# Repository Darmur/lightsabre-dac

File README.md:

# lightsabre-dac
Audiophile DAC for Raspberry Pi, based on ESS Sabre ES9018K2M

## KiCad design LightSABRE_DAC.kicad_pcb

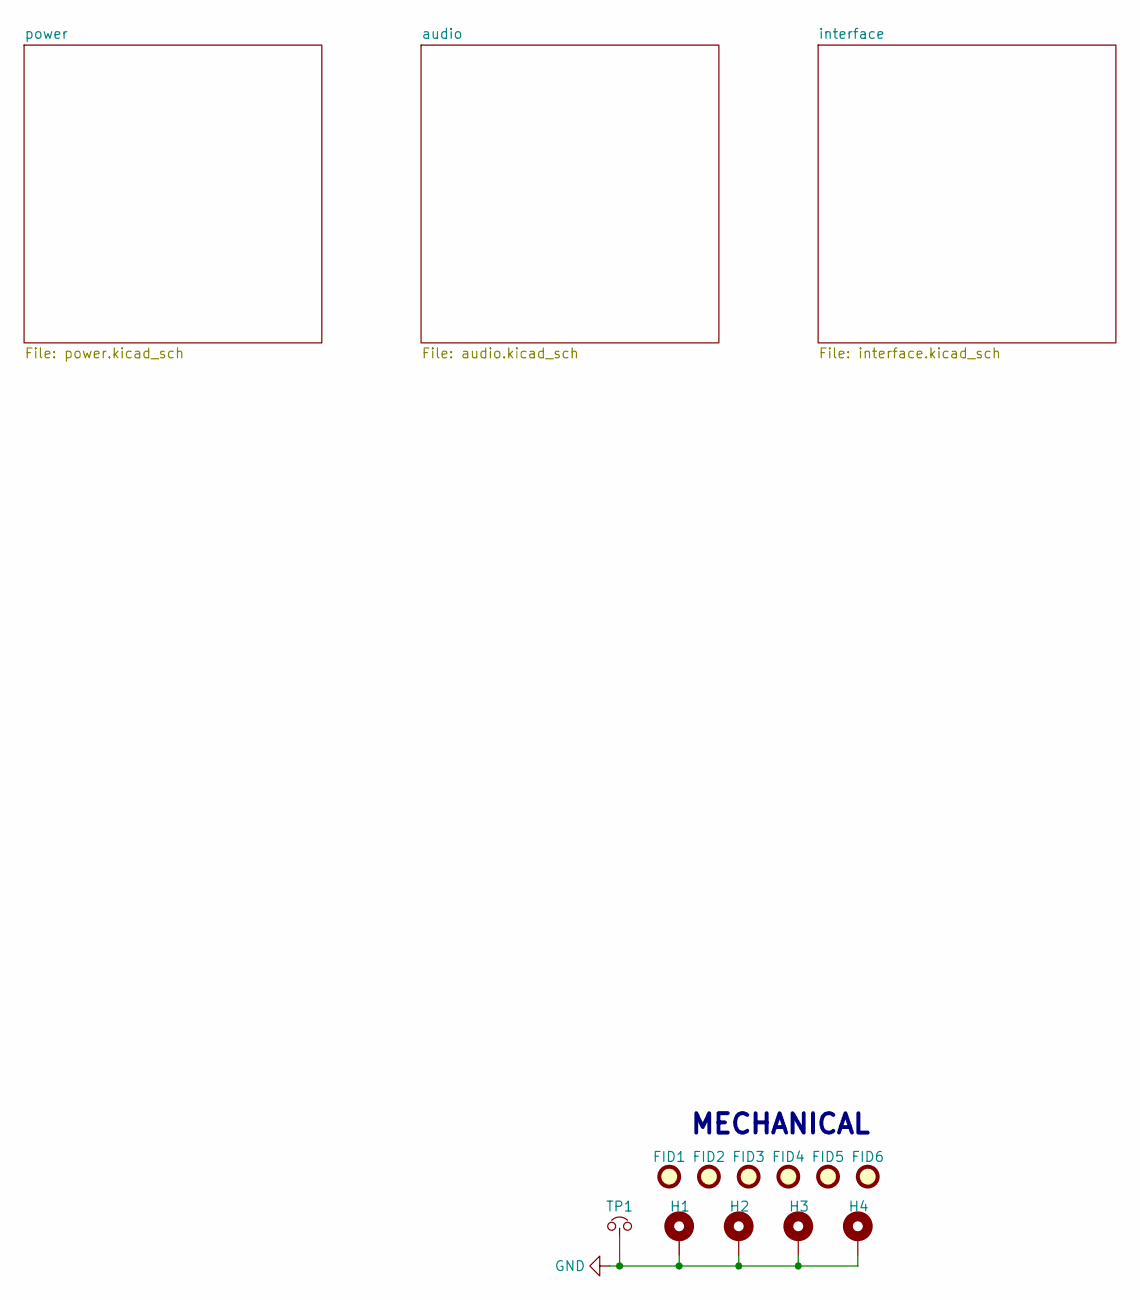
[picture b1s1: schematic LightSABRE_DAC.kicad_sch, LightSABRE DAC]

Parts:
FID1, FID2, FID3, FID4, FID5, FID6: FID_001; Fiducial_0.5mm_Mask1mm; MPN N.M.; LCSC N.M.
H1, H2, H3, H4: MOUNTING-HOLE-M2.5-SMALL; MOUNTING-HOLE-M2.5-ROUND-2.7MM-3.2MM; MPN N.M.; LCSC N.M.
TP1: GND-TP; TestPoint_Bridge_Pitch7.62mm_Drill1.3mm; MPN N.M.; LCSC N.M.

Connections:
GND: H1.1, H2.1, H3.1, H4.1, TP1.1; also elsewhere on the board

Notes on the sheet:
MECHANICAL

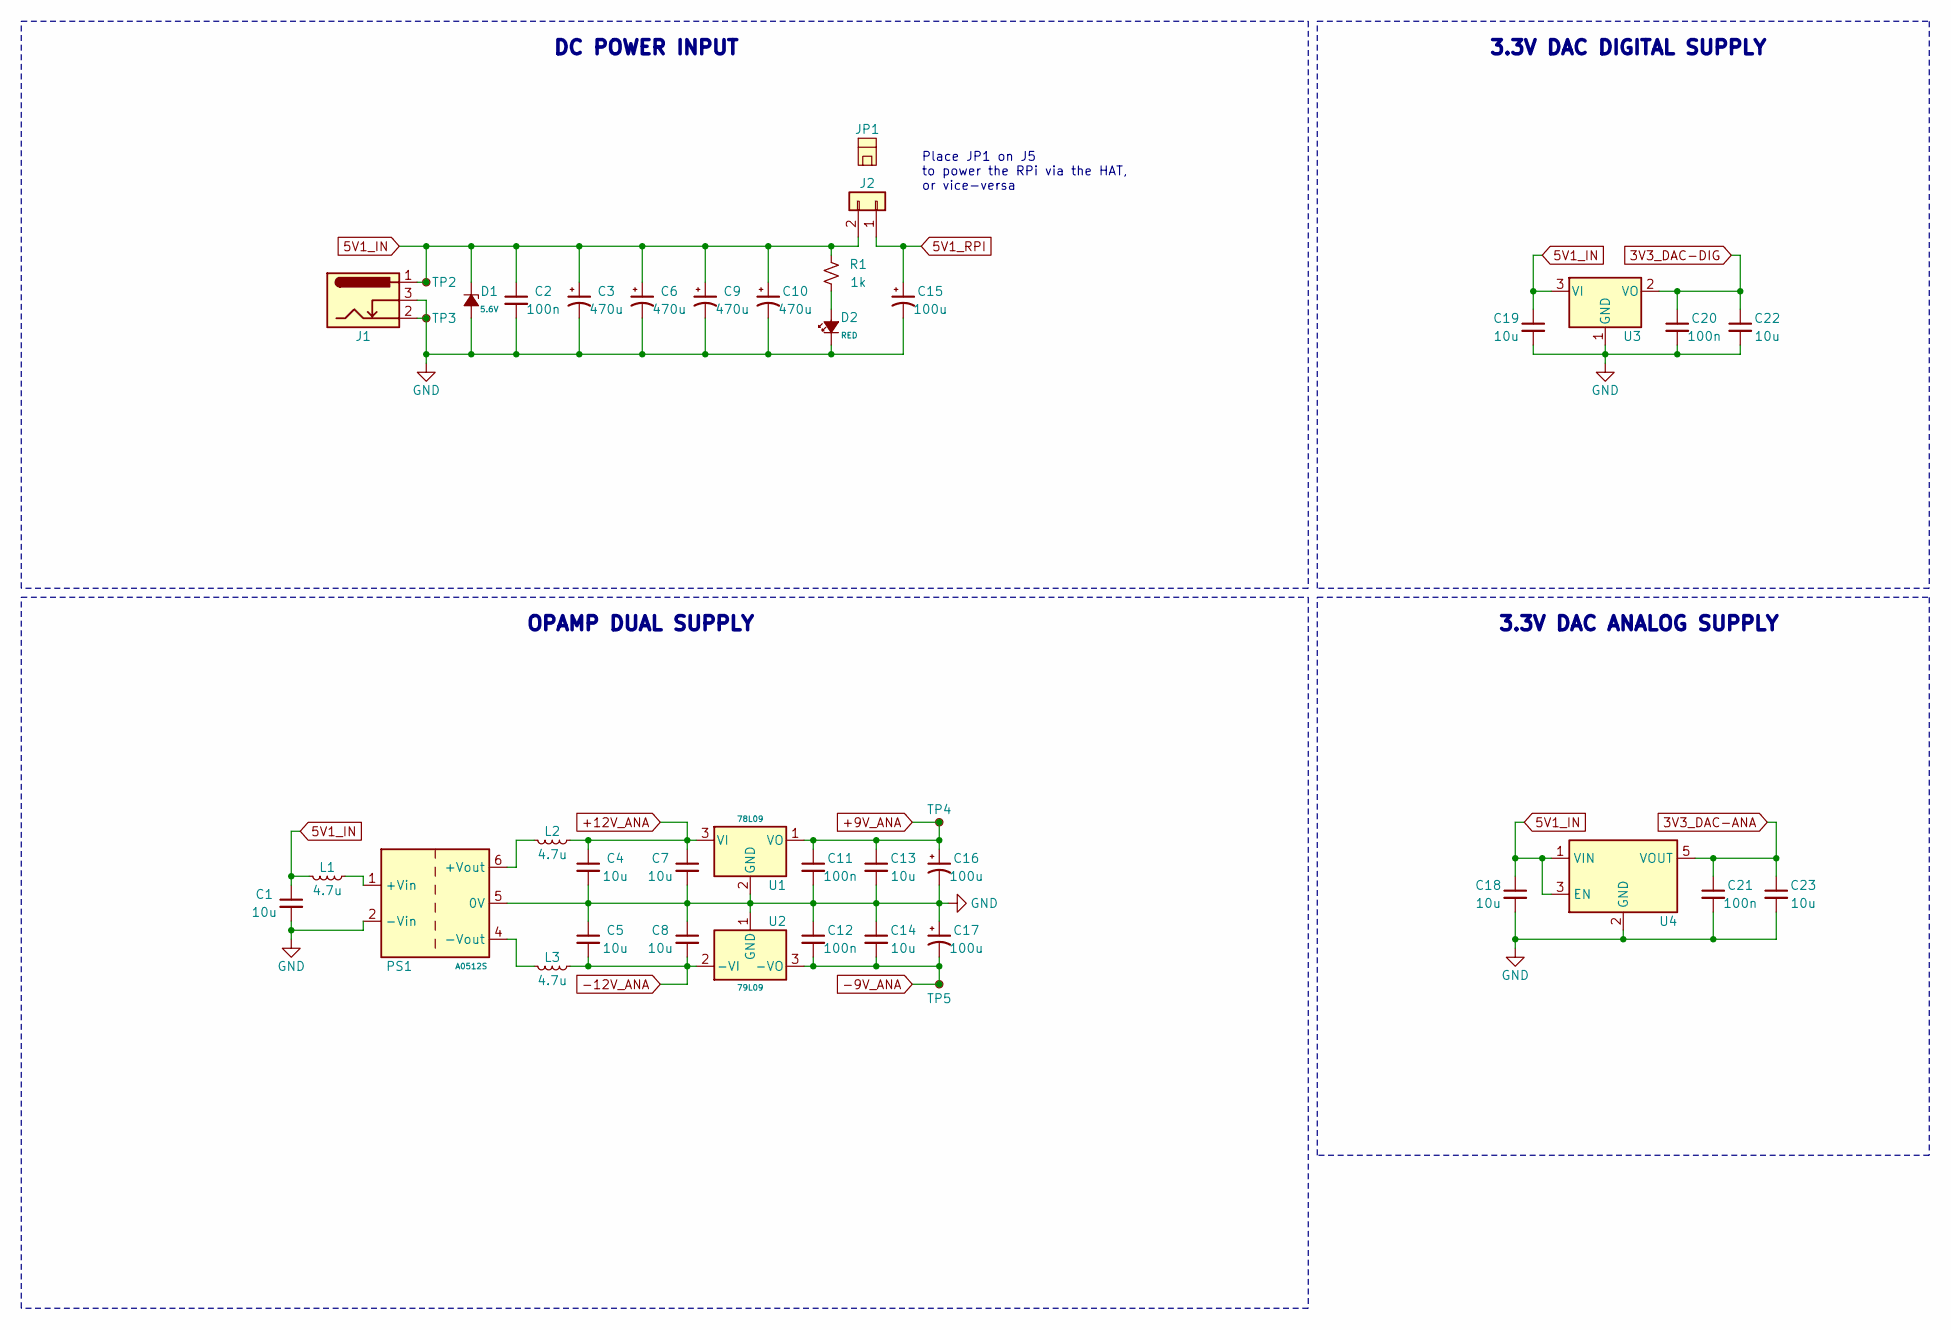
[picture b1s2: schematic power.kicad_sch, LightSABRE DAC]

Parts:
C1, C4, C5, C7, C8, C13, C14, C18, C19, C22, C23: CAP-10U-20%-16V-X5R-0603_004; C_0603_1608Metric; MPN HGC0603R5106M160NTHJ; LCSC C7472959
C2, C11, C12: CAP-100N-10%-50V-X7R-0603_002; C_0603_1608Metric; MPN CGA0603X7R104K500JT; LCSC C6119867
C3, C6, C9, C10: CAP-EL-470U-20%-10V-ALUM-6.3MM-7.7MM_002; CP_Elec_6.3x7.7; MPN RVT1A471M0607; LCSC C335982
C15, C16, C17: CAP-EL-100U-20%-16V-ALUM-5.0MM-5.4MM_002; CP_Elec_5x5.4; MPN RVT1C101M0505; LCSC C2977550
C20, C21: CAP-100N-10%-16V-X7R-0402_002; C_0402_1005Metric; MPN FCC0402B104K160AT; LCSC C5137468
D1: ZENER-5.6V-5W-SMB_003; D_SMB; Voltage 5.6V; MPN SMBJ5339B; LCSC C5122124
D2: LED-RED-0402_002; LED_0402_1005Metric; MPN XL-1005SURC; LCSC C25503345
J1: BARREL-JACK-SW_002; BarrelJack; MPN DC-005 5.5-2.0MM; LCSC C16214
J2: CONN-HDR-01X02-2.54-TH_002; PinHeader_2x01_P2.54mm_Vertical; MPN C124375; LCSC C124375
JP1: CONN-SHUNT-2P-2.54MM-BLACK-CAPPED_002; MPN HY-2540-B1NIB; LCSC C18185738
L1, L2, L3: IND-4.7U-20%-1.55A-0.196OHM-1008_002; L_1008_2520Metric; MPN WIP252012P-4R7ML; LCSC C964123
PS1: A0512S-2W-1.5KV-SIP_002; Converter_DCDC_XP_POWER-IHxxxxS_THT; MPN A0512S-2WR2; LCSC C5369424
R1: RES-1K-5%-0.063W-0402_002; R_0402_1005Metric; MPN 0402WGJ0102TCE; LCSC C25543
TP2, TP3, TP4, TP5: TP-TH-ROUND-1MM-0.5MM; TestPoint_THTPad_D1.0mm_Drill0.5mm; MPN N.M.; LCSC N.M.
U1: 78L09-SOT89_002; SOT-89-3; MPN 78L09; LCSC C22458782
U2: 79L09-SOT89_002; SOT-89-3; MPN PJ79L09SQ; LCSC C41784049
U3: LR6206B-U33; SOT-23; MPN LR6206B-U33; LCSC C5336486
U4: TPS7A2033-SOT23; SOT-23-5; MPN TPS7A2033PDBVR; LCSC C2862740

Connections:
3V3_DAC-ANA: C21.1, C23.1, U4.5 (VOUT); also elsewhere on the board
3V3_DAC-DIG: C20.1, C22.1, U3.2 (VO); also elsewhere on the board
5V1_IN: C1.1, C2.1, C3.1, C6.1, C9.1, C10.1, C18.1, C19.1, D1.1 (K), J1.1, J2.2, L1.2, R1.1, TP2.1, U3.3 (VI), U4.1 (VIN), U4.3 (EN); also elsewhere on the board
5V1_RPI: C15.1, J2.1; also elsewhere on the board
+9V_ANA: C11.1, C13.1, C16.1, TP4.1, U1.1 (VO); also elsewhere on the board
+12V_ANA: C4.1, C7.1, L2.1, U1.3 (VI)
-9V_ANA: C12.2, C14.2, C17.2, TP5.1, U2.3 (-VO); also elsewhere on the board
-12V_ANA: C5.2, C8.2, L3.1, U2.2 (-VI)
GND: C1.2, C2.2, C3.2, C4.2, C5.1, C6.2, C7.2, C8.1, C9.2, C10.2, C11.2, C12.1, C13.2, C14.1, C15.2, C16.2, C17.1, C18.2, C19.2, C20.2, C21.2, C22.2, C23.2, D1.2 (A), D2.1 (K), J1.2, J1.3, PS1.2 (-Vin), PS1.5 (0V), TP3.1, U1.2 (GND), U2.1 (GND), U3.1 (GND), U4.2 (GND); also elsewhere on the board
unnamed: D2.2 (A), R1.2
unnamed: L1.1, PS1.1 (+Vin)
unnamed: L2.2, PS1.6 (+Vout)
unnamed: L3.2, PS1.4 (-Vout)

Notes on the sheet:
DC POWER INPUT
3.3V DAC DIGITAL SUPPLY
OPAMP DUAL SUPPLY
3.3V DAC ANALOG SUPPLY
Place JP1 on J5 to power the RPi via the HAT, or vice-versa

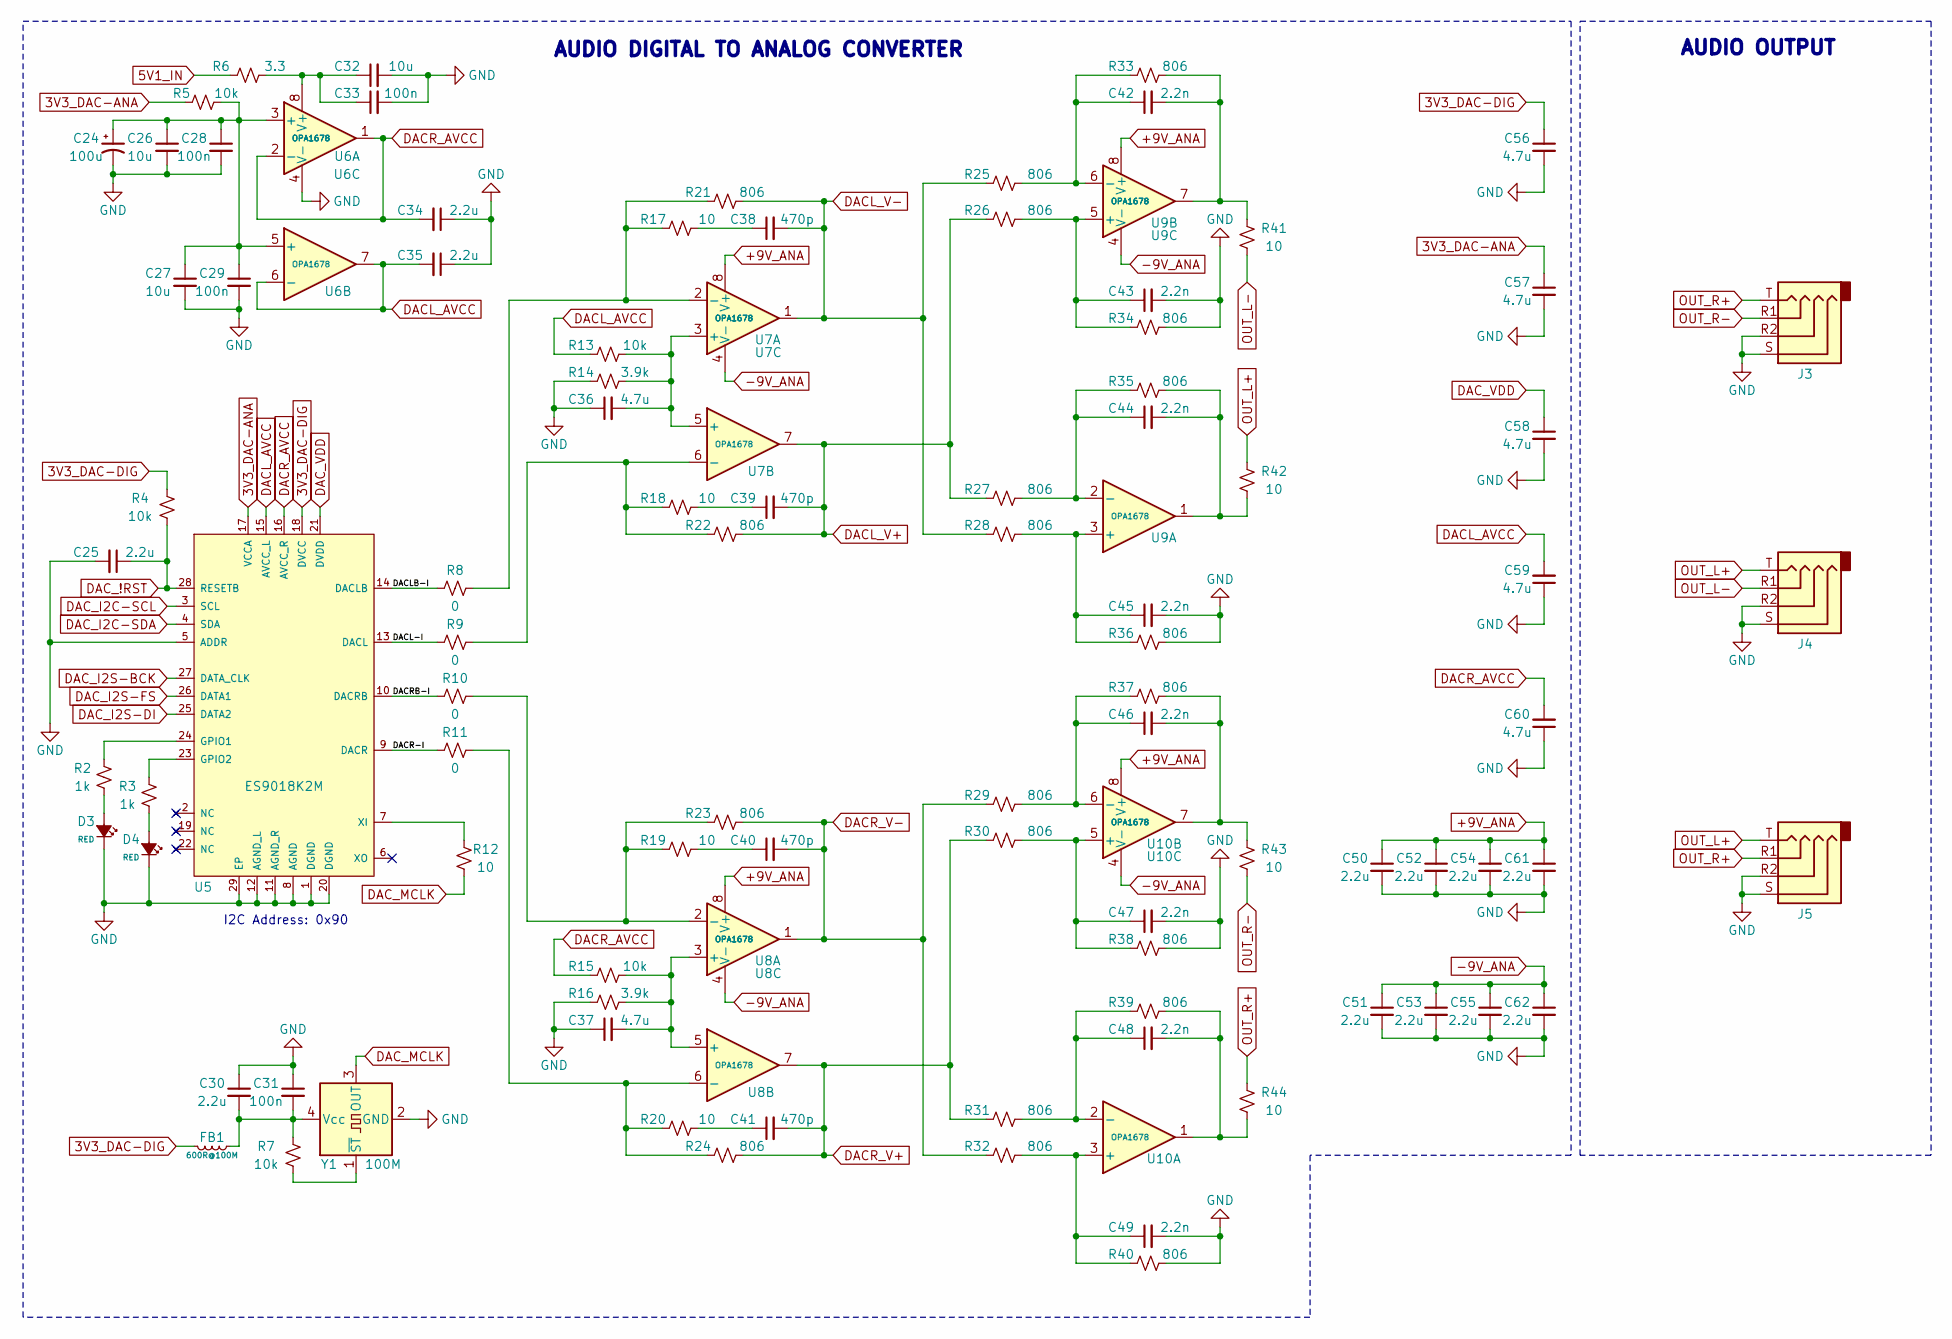
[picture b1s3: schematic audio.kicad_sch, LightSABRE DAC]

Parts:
C24: CAP-EL-100U-20%-16V-ALUM-5.0MM-5.4MM_002; CP_Elec_5x5.4; MPN RVT1C101M0505; LCSC C2977550
C25, C30, C34, C35, C50, C51, C52, C53, C54, C55, C61, C62: CAP-2.2U-20%-16V-X5R-0402_002; C_0402_1005Metric; MPN CGA0402X5R225M160GT; LCSC C6119773
C26, C27, C32: CAP-10U-20%-16V-X5R-0603_004; C_0603_1608Metric; MPN HGC0603R5106M160NTHJ; LCSC C7472959
C28, C29, C31, C33: CAP-100N-10%-16V-X7R-0402_002; C_0402_1005Metric; MPN FCC0402B104K160AT; LCSC C5137468
C36, C37, C56, C57, C58, C59, C60: CAP-4.7U-20%-10V-X5R-0402_002; C_0402_1005Metric; MPN HGC0402R5475M100NTEJ; LCSC C7472957
C38, C39, C40, C41: CAP-470P-5%-50V-C0G-0402_002; C_0402_1005Metric; MPN CGA0402C0G471J500GT; LCSC C20069335
C42, C43, C44, C45, C46, C47, C48, C49: CAP-2.2N-2%-50V-C0G-0402_001; C_0402_1005Metric; MPN GRM1555C1H222GA01D; LCSC C2987940
D3, D4: LED-RED-0402_002; LED_0402_1005Metric; MPN XL-1005SURC; LCSC C25503345
FB1: FERR-BEAD-600OHM@100MHZ-0.7A-0.34OHM-0402; L_0402_1005Metric; MPN PBY100505T-601Y-N; LCSC C142082
J3, J4, J5: PJ-320A; TRRS-PJ-320A; MPN PJ-320A; LCSC C2884926
R2, R3: RES-1K-5%-0.063W-0402_002; R_0402_1005Metric; MPN 0402WGJ0102TCE; LCSC C25543
R4, R5, R7, R13, R15: RES-10K-1%-0.063W-0402_002; R_0402_1005Metric; MPN RTT021002FTH; LCSC C102749
R6: RES-3.3-1%-0.1W-0603_002; R_0603_1608Metric; MPN FRC0603F3R30TS; LCSC C2930016
R8, R9, R10, R11: RES-0-1%-0.1W-0603_002; R_0603_1608Metric; MPN FRC0603F0000TS; LCSC C2906974
R12, R17, R18, R19, R20, R41, R42, R43, R44: RES-10-1%-0.063W-0402_002; R_0402_1005Metric; MPN FRC0402F10R0TS; LCSC C2906862
R14, R16: RES-3.9K-1%-0.063W-0402_002; R_0402_1005Metric; MPN FRC0402F3901TS; LCSC C2909346
R21, R22, R23, R24, R25, R26, R27, R28, R29, R30, R31, R32, R33, R34, R35, R36, R37, R38, R39, R40: RES-806-0.1%-0.063W-THIN-0402_001; R_0402_1005Metric; MPN RT0402BRD07806RL; LCSC C852922
U5: ES9018K2M; QFN-28-1EP_5x5mm_P0.5mm_EP3.25x3.25mm_ThermalVias_0.3mm; MPN ES9018K2M; LCSC C2688377
U6, U7, U8, U9, U10: OPA1678-VSSOP; MSOP-8_3x3mm_P0.65mm; MPN OPA1678IDGKR; LCSC C2863133
Y1: OSC-XO-100M-3225_002; Oscillator_SMD_4Pin_3.2x2.5mm; MPN O93225100MEDA4SI-13; LCSC C496694

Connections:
3V3_DAC-ANA: C57.1, R5.1, U5.17 (VCCA); also elsewhere on the board
3V3_DAC-DIG: C56.1, FB1.2, R4.1, U5.18 (DVCC); also elsewhere on the board
5V1_IN: R6.1; also elsewhere on the board
+9V_ANA: C50.1, C52.1, C54.1, C61.1, U7.8 (V+), U8.8 (V+), U9.8 (V+), U10.8 (V+); also elsewhere on the board
-9V_ANA: C51.1, C53.1, C55.1, C62.1, U7.4 (V-), U8.4 (V-), U9.4 (V-), U10.4 (V-); also elsewhere on the board
/audio/DACL-I: R9.2, U5.13 (DACL)
/audio/DACLB-I: R8.2, U5.14 (DACLB)
/audio/DACR-I: R11.2, U5.9 (DACR)
/audio/DACRB-I: R10.2, U5.10 (DACRB)
DACL_AVCC: C35.2, C59.2, R13.1, U5.15 (AVCC_L), U6.6 (-), U6.7
DACL_V+: C39.2, R22.2, R26.1, R27.1, U7.7
DACL_V-: C38.2, R21.2, R25.1, R28.1, U7.1
DACR_AVCC: C34.2, C60.2, R15.1, U5.16 (AVCC_R), U6.1, U6.2 (-)
DACR_V+: C41.2, R24.2, R30.1, R31.1, U8.7
DACR_V-: C40.2, R23.2, R29.1, R32.1, U8.1
DAC_!RST: C25.1, R4.2, U5.28 (RESETB)
DAC_I2C-SCL: U5.3 (SCL); also elsewhere on the board
DAC_I2C-SDA: U5.4 (SDA); also elsewhere on the board
DAC_I2S-BCK: U5.27 (DATA_CLK); also elsewhere on the board
DAC_I2S-DI: U5.25 (DATA2); also elsewhere on the board
DAC_I2S-FS: U5.26 (DATA1); also elsewhere on the board
DAC_MCLK: R12.2, Y1.3 (OUT)
DAC_VDD: C58.1, U5.21 (DVDD)
GND: C24.2, C25.2, C26.2, C27.2, C28.2, C29.2, C30.1, C31.1, C32.2, C33.2, C34.1, C35.1, C36.1, C37.1, C43.2, C45.2, C47.2, C49.2, C50.2, C51.2, C52.2, C53.2, C54.2, C55.2, C56.2, C57.2, C58.2, C59.1, C60.1, C61.2, C62.2, D3.1 (K), D4.1 (K), J3.R2, J3.S, J4.R2, J4.S, J5.R2, J5.S, R14.1, R16.1, R34.2, R36.2, R38.2, R40.2, U5.1 (DGND), U5.5 (ADDR), U5.8 (AGND), U5.11 (AGND_R), U5.12 (AGND_L), U5.20 (DGND), U5.29 (EP), U6.4 (V-), Y1.2 (GND); also elsewhere on the board
unnamed: C38.1, R17.2
unnamed: C39.1, R18.2
unnamed: C40.1, R19.2
unnamed: C41.1, R20.2
unnamed: C42.2, R33.2, R41.2, U9.7
unnamed: C44.2, R35.2, R42.1, U9.1
unnamed: C46.2, R37.2, R43.2, U10.7
unnamed: C48.2, R39.2, R44.1, U10.1
unnamed: D3.2 (A), R2.2
unnamed: D4.2 (A), R3.2
unnamed: R2.1, U5.24 (GPIO1)
unnamed: R3.1, U5.23 (GPIO2)
unnamed: R12.1, U5.7 (XI)
unnamed: C24.1, C26.1, C27.1, C28.1, C29.1, R5.2, U6.3 (+), U6.5 (+)
unnamed: C32.1, C33.1, R6.2, U6.8 (V+)
unnamed: C36.2, R13.2, R14.2, U7.3 (+), U7.5 (+)
unnamed: R8.1, R17.1, R21.1, U7.2 (-)
unnamed: R9.1, R18.1, R22.1, U7.6 (-)
unnamed: C37.2, R15.2, R16.2, U8.3 (+), U8.5 (+)
unnamed: R10.1, R19.1, R23.1, U8.2 (-)
unnamed: R11.1, R20.1, R24.1, U8.6 (-)
unnamed: C45.1, R28.2, R36.1, U9.3 (+)
unnamed: C44.1, R27.2, R35.1, U9.2 (-)
unnamed: C43.1, R26.2, R34.1, U9.5 (+)
unnamed: C42.1, R25.2, R33.1, U9.6 (-)
unnamed: C49.1, R32.2, R40.1, U10.3 (+)
unnamed: C48.1, R31.2, R39.1, U10.2 (-)
unnamed: C47.1, R30.2, R38.1, U10.5 (+)
unnamed: C46.1, R29.2, R37.1, U10.6 (-)
unnamed: C30.2, C31.2, FB1.1, R7.2, Y1.4 (Vcc)
unnamed: R7.1, Y1.1 (~ST)
OUT_L+: J4.T, J5.T, R42.2
OUT_L-: J4.R1, R41.1
OUT_R+: J3.T, J5.R1, R44.2
OUT_R-: J3.R1, R43.1

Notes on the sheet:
AUDIO OUTPUT
AUDIO DIGITAL TO ANALOG CONVERTER
I2C Address: 0x90

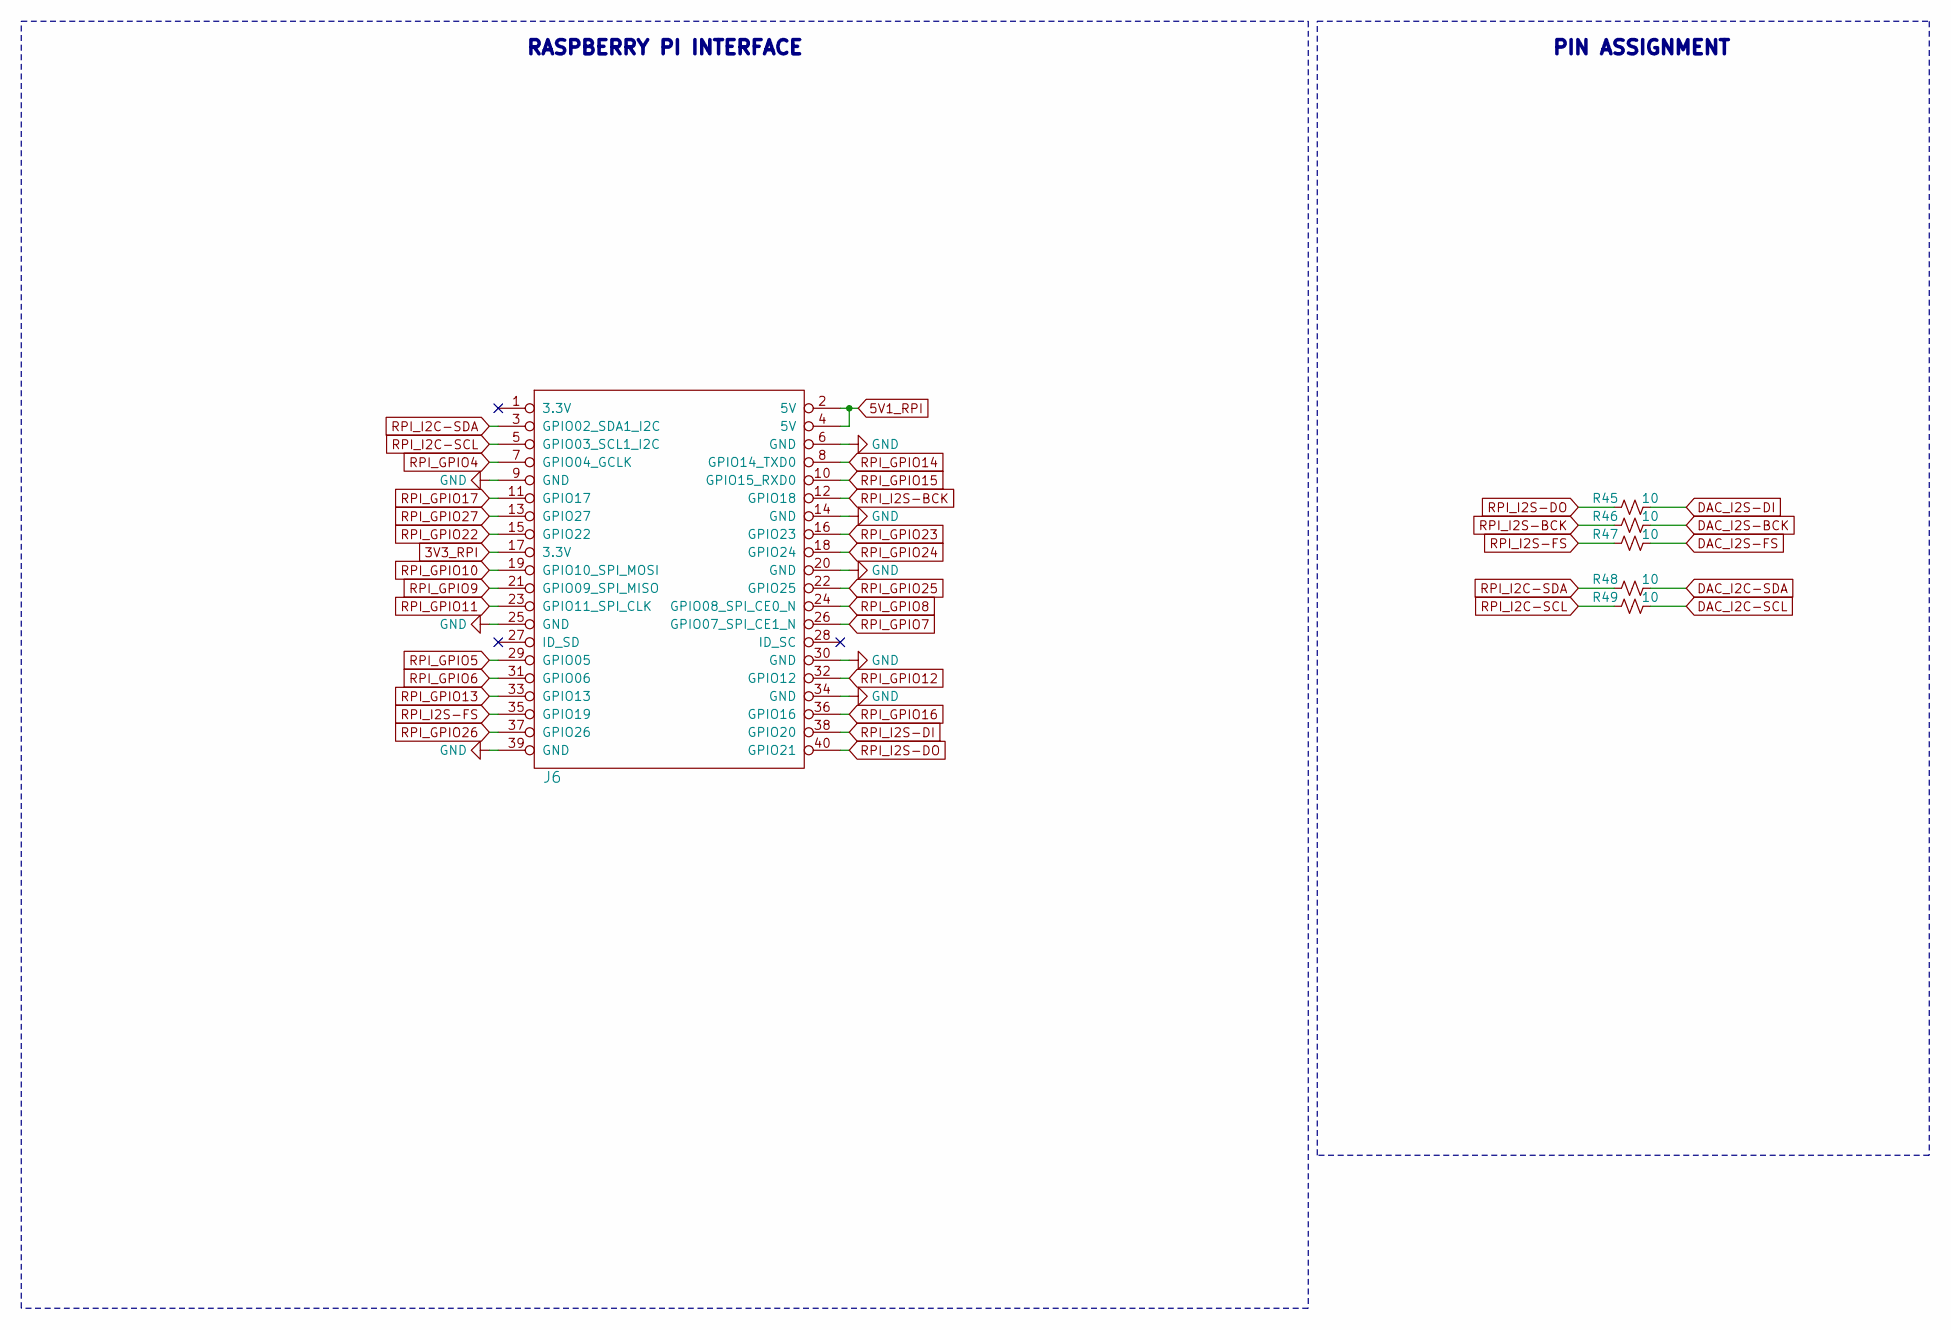
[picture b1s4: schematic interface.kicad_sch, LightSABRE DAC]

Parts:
J6: RPi-GPIO-SKT-TH-EXT_002; SKT-02x20-TH-EXT; MPN 2.54-2*20PPC104; LCSC C35165
R45, R46, R47, R48, R49: RES-10-1%-0.063W-0402_002; R_0402_1005Metric; MPN FRC0402F10R0TS; LCSC C2906862

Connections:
3V3_RPI: J6.17 (3.3V)
5V1_RPI: J6.2 (5V), J6.4 (5V); also elsewhere on the board
DAC_I2C-SCL: R49.2; also elsewhere on the board
DAC_I2C-SDA: R48.2; also elsewhere on the board
DAC_I2S-BCK: R46.2; also elsewhere on the board
DAC_I2S-DI: R45.2; also elsewhere on the board
DAC_I2S-FS: R47.2; also elsewhere on the board
GND: J6.6 (GND), J6.9 (GND), J6.14 (GND), J6.20 (GND), J6.25 (GND), J6.30 (GND), J6.34 (GND), J6.39 (GND); also elsewhere on the board
RPI_GPIO4: J6.7 (GPIO04_GCLK)
RPI_GPIO5: J6.29 (GPIO05)
RPI_GPIO6: J6.31 (GPIO06)
RPI_GPIO7: J6.26 (GPIO07_SPI_CE1_N)
RPI_GPIO8: J6.24 (GPIO08_SPI_CE0_N)
RPI_GPIO9: J6.21 (GPIO09_SPI_MISO)
RPI_GPIO10: J6.19 (GPIO10_SPI_MOSI)
RPI_GPIO11: J6.23 (GPIO11_SPI_CLK)
RPI_GPIO12: J6.32 (GPIO12)
RPI_GPIO13: J6.33 (GPIO13)
RPI_GPIO14: J6.8 (GPIO14_TXD0)
RPI_GPIO15: J6.10 (GPIO15_RXD0)
RPI_GPIO16: J6.36 (GPIO16)
RPI_GPIO17: J6.11 (GPIO17)
RPI_GPIO22: J6.15 (GPIO22)
RPI_GPIO23: J6.16 (GPIO23)
RPI_GPIO24: J6.18 (GPIO24)
RPI_GPIO25: J6.22 (GPIO25)
RPI_GPIO26: J6.37 (GPIO26)
RPI_GPIO27: J6.13 (GPIO27)
RPI_I2C-SCL: J6.5 (GPIO03_SCL1_I2C), R49.1
RPI_I2C-SDA: J6.3 (GPIO02_SDA1_I2C), R48.1
RPI_I2S-BCK: J6.12 (GPIO18), R46.1
RPI_I2S-DI: J6.38 (GPIO20)
RPI_I2S-DO: J6.40 (GPIO21), R45.1
RPI_I2S-FS: J6.35 (GPIO19), R47.1

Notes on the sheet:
PIN ASSIGNMENT
RASPBERRY PI INTERFACE

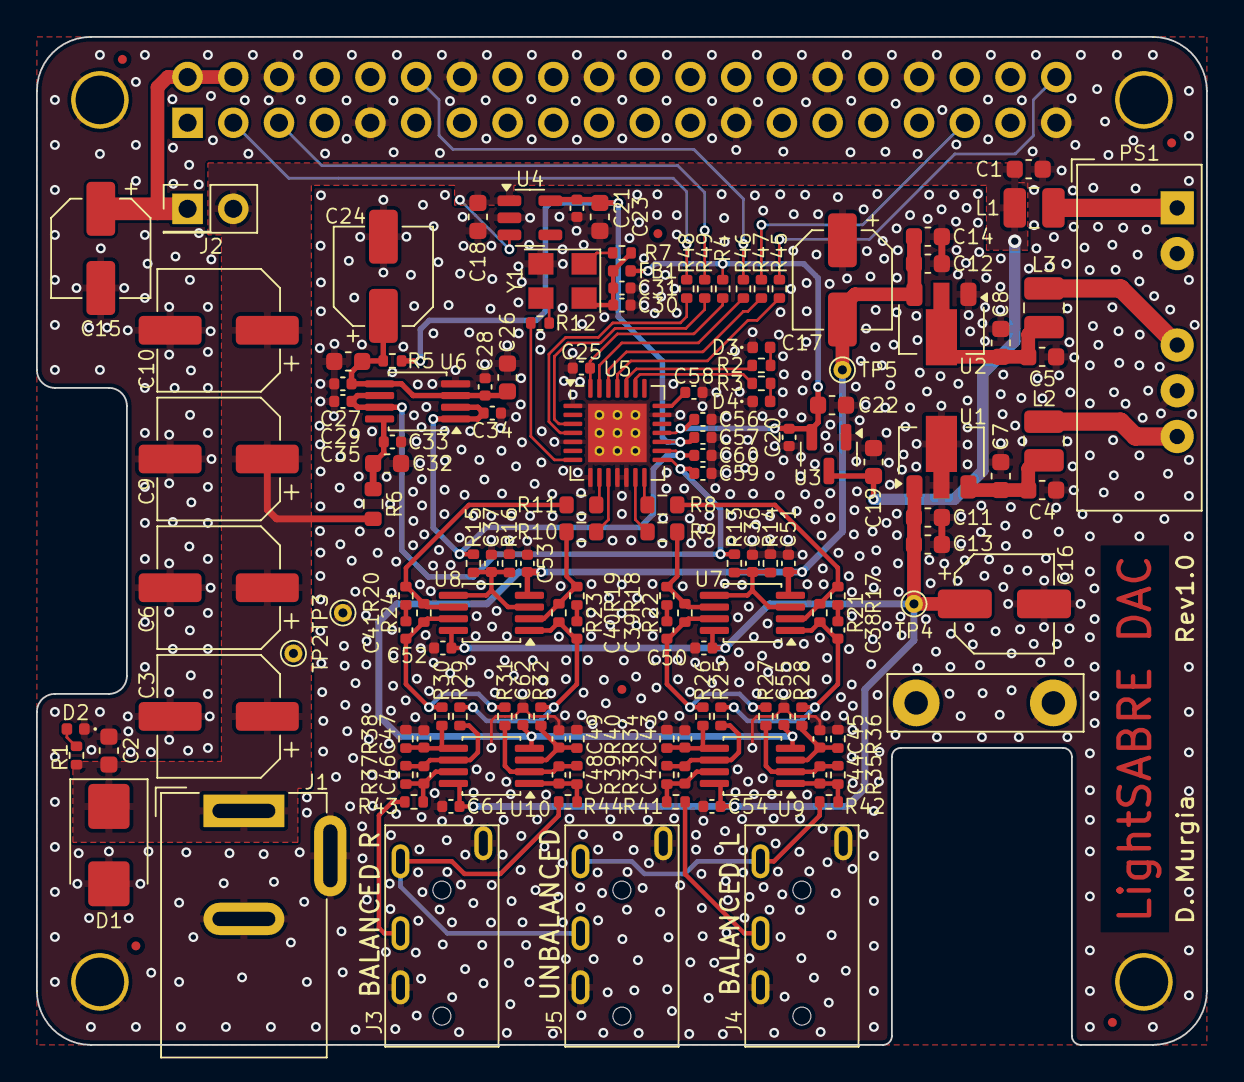
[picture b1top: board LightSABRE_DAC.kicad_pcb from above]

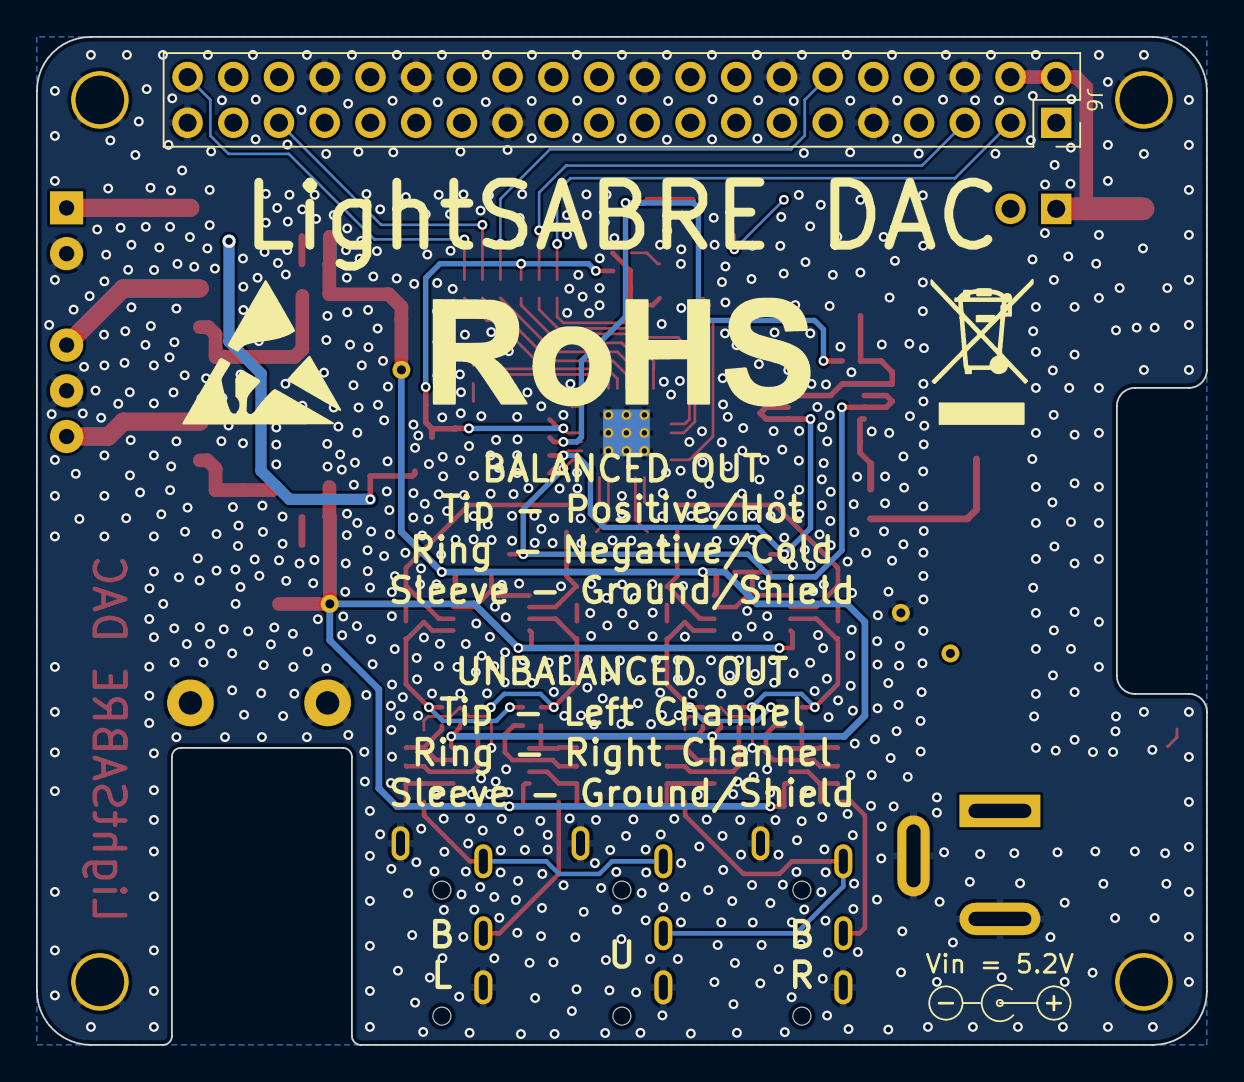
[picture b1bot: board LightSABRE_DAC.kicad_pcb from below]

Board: 4 copper layers, 65.0 x 56.0 mm, 156 parts (5 on the bottom side), 71 nets.

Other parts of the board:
GFX1: Symbol_Barrel_Polarity
GFX2: WEEE-Logo_5.6x8mm_SilkScreen
GFX3: ESD-Logo_8.9x8mm_SilkScreen
GFX4: RoHS-Logo_6mm_SilkScreen

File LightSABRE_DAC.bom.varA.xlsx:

Qty | Reference | Descr | MPN | Footprint | Datasheet | Value | MOUSER | DIGIKEY | LCSC
14 | C1, C4, C5, C7, C8, C13, C14, C18, C19, C22, C23, C26, C27, C32 | CAP CER 10UF 20% 16V X5R 0603 | HGC0603R5106M160NTHJ | Capacitor_SMD:C_0603_1608Metric | ~ | CAP-10U-20%-16V-X5R-0603_004 | - | - | C7472959
3 | C2, C11, C12 | CAP CER 100NF 10% 50V X7R 0603 | CGA0603X7R104K500JT | Capacitor_SMD:C_0603_1608Metric | ~ | CAP-100N-10%-50V-X7R-0603_002 | - | - | C6119867
4 | C3, C6, C9, C10 | CAP ALUM 470UF 20% 10V SMD | RVT1A471M0607 | Capacitor_SMD:CP_Elec_6.3x7.7 | https://www.lcsc.com/datasheet/lcsc_datasheet_2411220152_ROQ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 | CAP-EL-470U-20%-10V-ALUM-6.3MM-7.7MM_002 | - | - | C335982
4 | C15, C16, C17, C24 | CAP ALUM 100UF 20% 16V SMD | RVT1C101M0505 | Capacitor_SMD:CP_Elec_5x5.4 | https://www.lcsc.com/datasheet/lcsc_datasheet_2411121455_ROQ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 | CAP-EL-100U-20%-16V-ALUM-5.0MM-5.4MM_002 | - | - | C2977550
6 | C20, C21, C28, C29, C31, C33 | CAP CER 100NF 10% 16V X7R 0402 | FCC0402B104K160AT | Capacitor_SMD:C_0402_1005Metric | ~ | CAP-100N-10%-16V-X7R-0402_002 | - | - | C5137468
12 | C25, C30, C34, C35, C50, C51, C52, C53, C54, C55, C61, C62 | CAP CER 2.2UF 20% 16V X5R 0402 | CGA0402X5R225M160GT | Capacitor_SMD:C_0402_1005Metric | ~ | CAP-2.2U-20%-16V-X5R-0402_002 | - | - | C6119773
7 | C36, C37, C56, C57, C58, C59, C60 | CAP CER 4.7UF 20% 10V X5R 0402 | HGC0402R5475M100NTEJ | Capacitor_SMD:C_0402_1005Metric | ~ | CAP-4.7U-20%-10V-X5R-0402_002 | - | - | C7472957
4 | C38, C39, C40, C41 | CAP CER 470PF 5% 50V C0G 0402 | CGA0402C0G471J500GT | Capacitor_SMD:C_0402_1005Metric | ~ | CAP-470P-5%-50V-C0G-0402_002 | - | - | C20069335
8 | C42, C43, C44, C45, C46, C47, C48, C49 | CAP CER 2.2NF 2% 50V C0G 0402 | GRM1555C1H222GA01D | Capacitor_SMD:C_0402_1005Metric | ~ | CAP-2.2N-2%-50V-C0G-0402_001 | 81-GRM1555C1H222GA1D | 490-GRM1555C1H222GA01DCT-ND | C2987940
1 | D1 | DIODE ZENER 5.6V 5W SMB | SMBJ5339B | Diode_SMD:D_SMB | https://datasheet.lcsc.com/lcsc/2207271730_LGE-SMBJ5339B_C51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 | ZENER-5.6V-5W-SMB_003 | - | - | C5122124
3 | D2, D3, D4 | LED RED CLEAR 0402 | XL-1005SURC | LED_SMD:LED_0402_1005Metric | https://www.lcsc.com/datasheet/C25503345.pdf | LED-RED-0402_002 | - | - | C25503345
1 | FB1 | FERRITE BEAD 600OHM@100MHZ 0.7A 0.34OHM 0402 | PBY100505T-601Y-N | Inductor_SMD:L_0402_1005Metric | https://datasheet.lcsc.com/lcsc/1811141621_Chilisin-Elec-PBY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 | FERR-BEAD-600OHM@100MHZ-0.7A-0.34OHM-0402 | - | - | C142082
1 | J1 | DC BARREL JACK 5.5X2.0MM TH | DC-005 5.5-2.0MM | dm_CONN:BarrelJack | https://datasheet.lcsc.com/lcsc/1811051112_BOOMELE-Boom-Prec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 | BARREL-JACK-SW_002 | - | - | C16214
1 | J2 | CONN HEADER TH 2POS 01X02 2.54MM | C124375 | Connector_PinHeader_2.54mm:PinHeader_2x01_P2.54mm_Vertical | https://datasheet.lcsc.com/szlcsc/1811151421_Ckmtw-Shenzhen-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 | CONN-HDR-01X02-2.54-TH_002 | - | - | C124375
3 | J3, J4, J5 | AUDIO JACK 3.5" 4 POLES TRRS TH | PJ-320A | dm_CONN:TRRS-PJ-320A | https://datasheet.lcsc.com/szlcsc/1912111437_SHOU-HAN-PJ-320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 | PJ-320A | - | - | C2884926
1 | J6 | CONN SOCKET TH 40POS 02X20 2.54MM EXT PIN | 2.54-2*20PPC104 | dm_CONN:SKT-02x20-TH-EXT | https://www.lcsc.com/datasheet/lcsc_datasheet_1811132110_BOO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 | RPi-GPIO-SKT-TH-EXT_002 | - | - | C35165
1 | JP1 | CONN SHUNT 2POS 2.54MM BLACK CAPPED | HY-2540-B1NIB |  | https://www.lcsc.com/datasheet/lcsc_datasheet_2410122012_Han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 | CONN-SHUNT-2P-2.54MM-BLACK-CAPPED_002 | - | - | C18185738
3 | L1, L2, L3 | IND 4.7 UH 20% 1.55A 0.196 OHM 1008 | WIP252012P-4R7ML | dm_SMD:L_1008_2520Metric | https://www.lcsc.com/datasheet/lcsc_datasheet_2410121513_INP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 | IND-4.7U-20%-1.55A-0.196OHM-1008_002 | - | - | C964123
1 | PS1 | ISOLATED DC DC CONVERTER 5V DUAL OUT+/-12V 2W SIP | A0512S-2WR2 | Converter_DCDC:Converter_DCDC_XP_POWER-IHxxxxS_THT | https://www.lcsc.com/datasheet/lcsc_datasheet_2401211050_YLP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 | A0512S-2W-1.5KV-SIP_002 | - | - | C5369424
3 | R1, R2, R3 | RES 1K OHM 5% 1/16W 0402 | 0402WGJ0102TCE | Resistor_SMD:R_0402_1005Metric | ~ | RES-1K-5%-0.063W-0402_002 | - | - | C25543
5 | R4, R5, R7, R13, R15 | RES 10K OHM 1% 1/16W 0402 | RTT021002FTH | Resistor_SMD:R_0402_1005Metric | ~ | RES-10K-1%-0.063W-0402_002 | - | - | C102749
1 | R6 | RES 3.3 OHM 1% 1/10W 0603 | FRC0603F3R30TS | Resistor_SMD:R_0603_1608Metric | ~ | RES-3.3-1%-0.1W-0603_002 | - | - | C2930016
4 | R8, R9, R10, R11 | RES 0 OHM 1% 1/16W 0603 | FRC0603F0000TS | Resistor_SMD:R_0603_1608Metric | ~ | RES-0-1%-0.1W-0603_002 | - | - | C2906974
14 | R12, R17, R18, R19, R20, R41, R42, R43, R44, R45, R46, R47, R48, R49 | RES 10 OHM 1% 1/16W 0402 | FRC0402F10R0TS | Resistor_SMD:R_0402_1005Metric | ~ | RES-10-1%-0.063W-0402_002 | - | - | C2906862
2 | R14, R16 | RES 3.9K OHM 1% 1/16W 0402 | FRC0402F3901TS | Resistor_SMD:R_0402_1005Metric | ~ | RES-3.9K-1%-0.063W-0402_002 | - | - | C2909346
20 | R21, R22, R23, R24, R25, R26, R27, R28, R29, R30, R31, R32, R33, R34, R35, R36,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 | RES 806 OHM 0.1% 1/16W THIN FILM 0402 | RT0402BRD07806RL | Resistor_SMD:R_0402_1005Metric | ~ | RES-806-0.1%-0.063W-THIN-0402_001 | 603-RT0402BRD07806RL | YAG1481CT-ND | C852922
1 | U1 | IC REG LINEAR 9V 100MA SOT89-3 | 78L09 | dm_SMD:SOT-89-3 | https://www.lcsc.com/datasheet/lcsc_datasheet_2410121529_HL-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 | 78L09-SOT89_002 | - | - | C22458782
1 | U2 | IC REG LINEAR -9V 100MA SOT89-3 | PJ79L09SQ | dm_SMD:SOT-89-3 | https://www.lcsc.com/datasheet/lcsc_datasheet_2410221617_PJS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 | 79L09-SOT89_002 | - | - | C41784049
1 | U3 | IC REG LINEAR 3.3V 300MA SOT23-3 | LR6206B-U33 | Package_TO_SOT_SMD:SOT-23 | https://www.lcsc.com/datasheet/lcsc_datasheet_2212192008_LR-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 | LR6206B-U33 | - | - | C5336486
1 | U4 | IC REG LINEAR 3.3V 300MA LOW-NOISE SOT23-5 | TPS7A2033PDBVR | Package_TO_SOT_SMD:SOT-23-5 | https://www.ti.com/lit/ds/symlink/tps7a20.pdf | TPS7A2033-SOT23 | 595-TPS7A2033PDBVR | 296-TPS7A2033PDBVRCT-ND | C2862740
1 | U5 | IC DAC 16/24/32BIT 384K DSD256 QFN28 | ES9018K2M | dm_SMD:QFN-28-1EP_5x5mm_P0.5mm_EP3.25x3.25mm_ThermalVias_0.3mm | https://www.mouser.com/datasheet/3/3763/1/ES9018K2M-Datashee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 | ES9018K2M | 460-ES9018K2M | - | C2688377
5 | U6, U7, U8, U9, U10 | IC OPAMP AUDIO 2 CIRCUIT 4.5V/36V VSSOP-8 | OPA1678IDGKR | Package_SO:MSOP-8_3x3mm_P0.65mm | https://www.ti.com/lit/ds/symlink/opa1678.pdf | OPA1678-VSSOP | 595-OPA1678IDGKR | 296-47667-1-ND | C2863133
1 | Y1 | OSC 3.3V 100MHZ 20PPM 3225 | O93225100MEDA4SI-13 | dm_SMD:Oscillator_SMD_4Pin_3.2x2.5mm | https://www.lcsc.com/datasheet/C496694.pdf | OSC-XO-100M-3225_002 | - | - | C496694

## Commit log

2026-02-21 add project files
